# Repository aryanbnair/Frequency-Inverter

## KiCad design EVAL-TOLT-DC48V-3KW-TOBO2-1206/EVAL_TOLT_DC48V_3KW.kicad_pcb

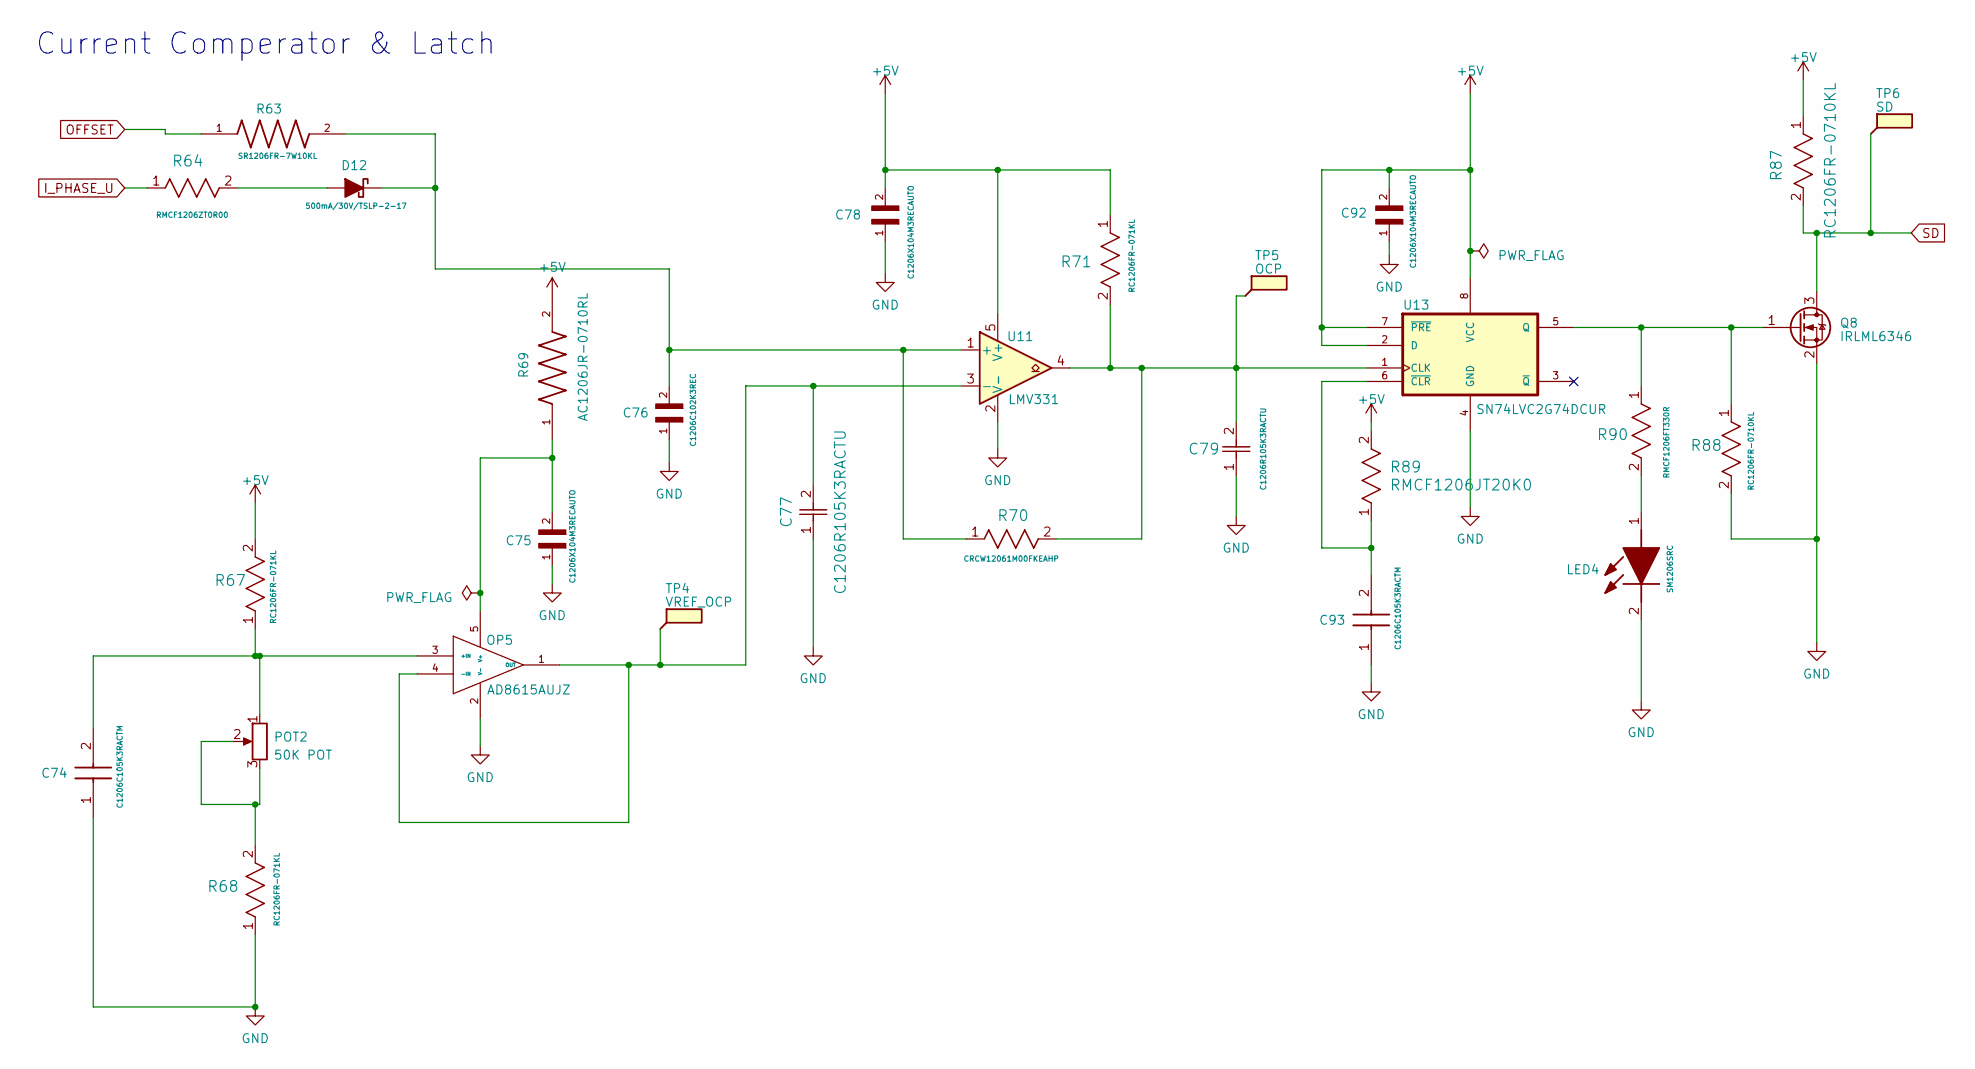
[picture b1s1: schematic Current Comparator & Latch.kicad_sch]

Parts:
C74, C93: C1206C105K3RACTM; C_1206_3216Metric; Mouser Part Number 80-C1206C105K3RACTM
C75, C78, C92: C1206X104M3RECAUTO; C_1206_3216Metric
C76: C1206C102K3REC; C_1206_3216Metric
C77, C79: C1206R105K3RACTU; C_1206_3216Metric
D12: 500mA/30V/TSLP-2-17; D_1206_3216Metric_Pad1.42x1.75mm_HandSolder
LED4: SM1206SRC; LED4; Mouser Part Number 749-SM1206SRC
OP5: AD8615AUJZ; AD8615; MPN AD8615AUJZ
POT2: 50K POT; POT2
Q8: IRLML6346; IRLML6346TRPBF
R63: SR1206FR-7W10KL; R_1206_3216Metric_Pad1.30x1.75mm_HandSolder
R64: RMCF1206ZT0R00; R_1206_3216Metric_Pad1.30x1.75mm_HandSolder
R67, R68, R71: RC1206FR-071KL; R_1206_3216Metric_Pad1.30x1.75mm_HandSolder
R69: AC1206JR-0710RL; R_1206_3216Metric_Pad1.30x1.75mm_HandSolder
R70: CRCW12061M00FKEAHP; R_1206_3216Metric_Pad1.30x1.75mm_HandSolder
R87, R88: RC1206FR-0710KL; R_1206_3216Metric_Pad1.30x1.75mm_HandSolder
R89: RMCF1206JT20K0; R_1206_3216Metric_Pad1.30x1.75mm_HandSolder
R90: RMCF1206FT330R; R_1206_3216Metric_Pad1.30x1.75mm_HandSolder
TP4: VREF_OCP; TestPoint_Bridge_Pitch2.54mm_Drill0.7mm
TP5: OCP; TestPoint_Bridge_Pitch2.54mm_Drill0.7mm
TP6: SD; TestPoint_Bridge_Pitch2.54mm_Drill0.7mm
U11: LMV331; LMV331M5
U13: SN74LVC2G74DCUR; SN74LVC2G74MDCUTEP

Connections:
+5V: C78.2, C92.2, R67.2, R69.2, R71.1, R87.1, R89.2, U11.5 (V+), U13.2 (D), U13.7 (~PRE), U13.8 (VCC); also elsewhere on the board
GND: C74.1, C75.1, C76.1, C77.1, C78.1, C79.1, C92.1, C93.1, LED4.2 (K), OP5.2 (V-), Q8.2 (S), R68.1, R88.2, U11.2 (V-), U13.4 (GND); also elsewhere on the board
I_PHASE_U: R64.1; also elsewhere on the board
unnamed: D12.2 (A), R64.2
unnamed: C76.2, D12.1 (K), R63.2, R70.1, U11.1 (+)
unnamed: LED4.1 (A), R90.2
unnamed: C74.2, OP5.3 (+IN), POT2.1, R67.1
unnamed: C77.2, OP5.1 (OUT), OP5.4 (-IN), TP4.1, U11.3 (-)
unnamed: C75.2, OP5.5 (V+), R69.1
unnamed: POT2.2, POT2.3, R68.2
unnamed: Q8.1 (G), R88.1, R90.1, U13.5 (Q)
unnamed: C79.2, R70.2, R71.2, TP5.1, U11.4, U13.1 (CLK)
unnamed: C93.2, R89.1, U13.6 (~CLR)
OFFSET: R63.1; also elsewhere on the board
SD: Q8.3 (D), R87.2, TP6.1; also elsewhere on the board

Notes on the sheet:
Current Comperator & Latch

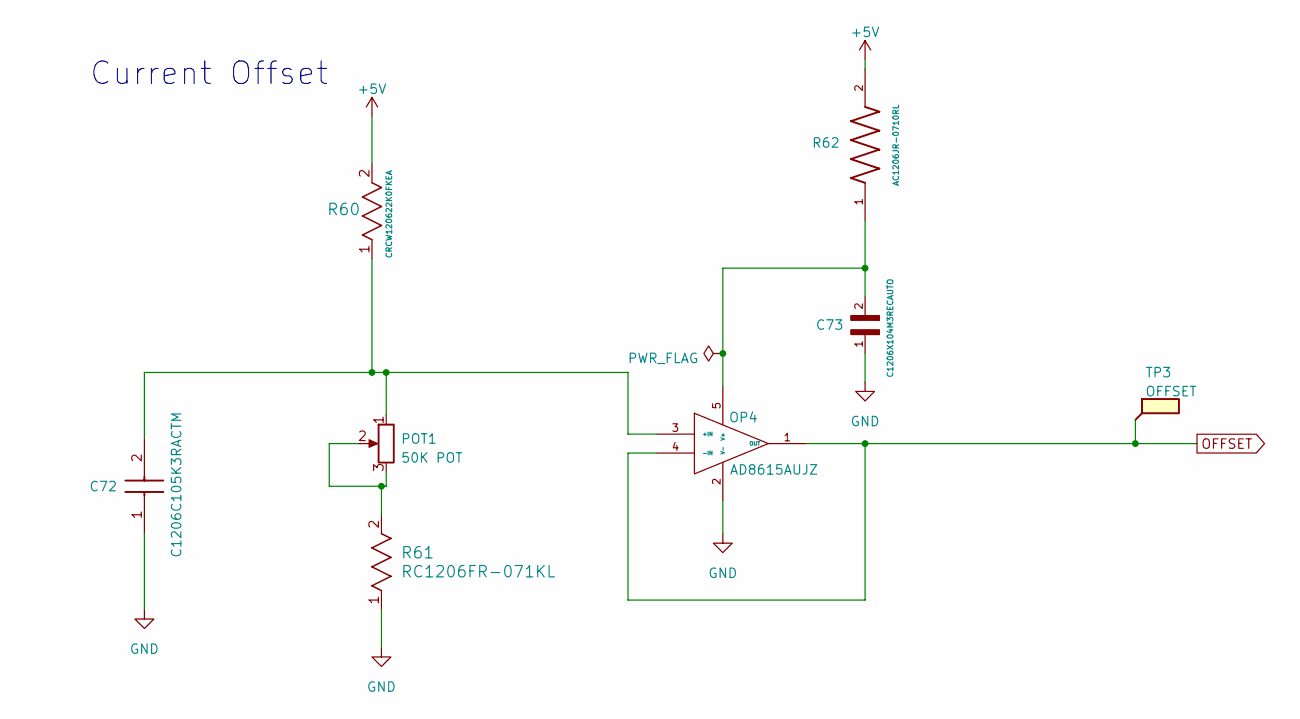
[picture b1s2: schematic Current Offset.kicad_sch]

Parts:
C72: C1206C105K3RACTM; C_1206_3216Metric; Mouser Part Number 80-C1206C105K3RACTM
C73: C1206X104M3RECAUTO; C_1206_3216Metric
OP4: AD8615AUJZ; AD8615; MPN AD8615AUJZ
POT1: 50K POT; POT2
R60: CRCW120622K0FKEA; R_1206_3216Metric_Pad1.30x1.75mm_HandSolder
R61: RC1206FR-071KL; R_1206_3216Metric_Pad1.30x1.75mm_HandSolder
R62: AC1206JR-0710RL; R_1206_3216Metric_Pad1.30x1.75mm_HandSolder
TP3: OFFSET; TestPoint_Bridge_Pitch2.54mm_Drill0.7mm

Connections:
+5V: R60.2, R62.2; also elsewhere on the board
GND: C72.1, C73.1, OP4.2 (V-), R61.1; also elsewhere on the board
unnamed: C72.2, OP4.3 (+IN), POT1.1, R60.1
unnamed: C73.2, OP4.5 (V+), R62.1
unnamed: POT1.2, POT1.3, R61.2
OFFSET: OP4.1 (OUT), OP4.4 (-IN), TP3.1; also elsewhere on the board

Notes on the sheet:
Current Offset

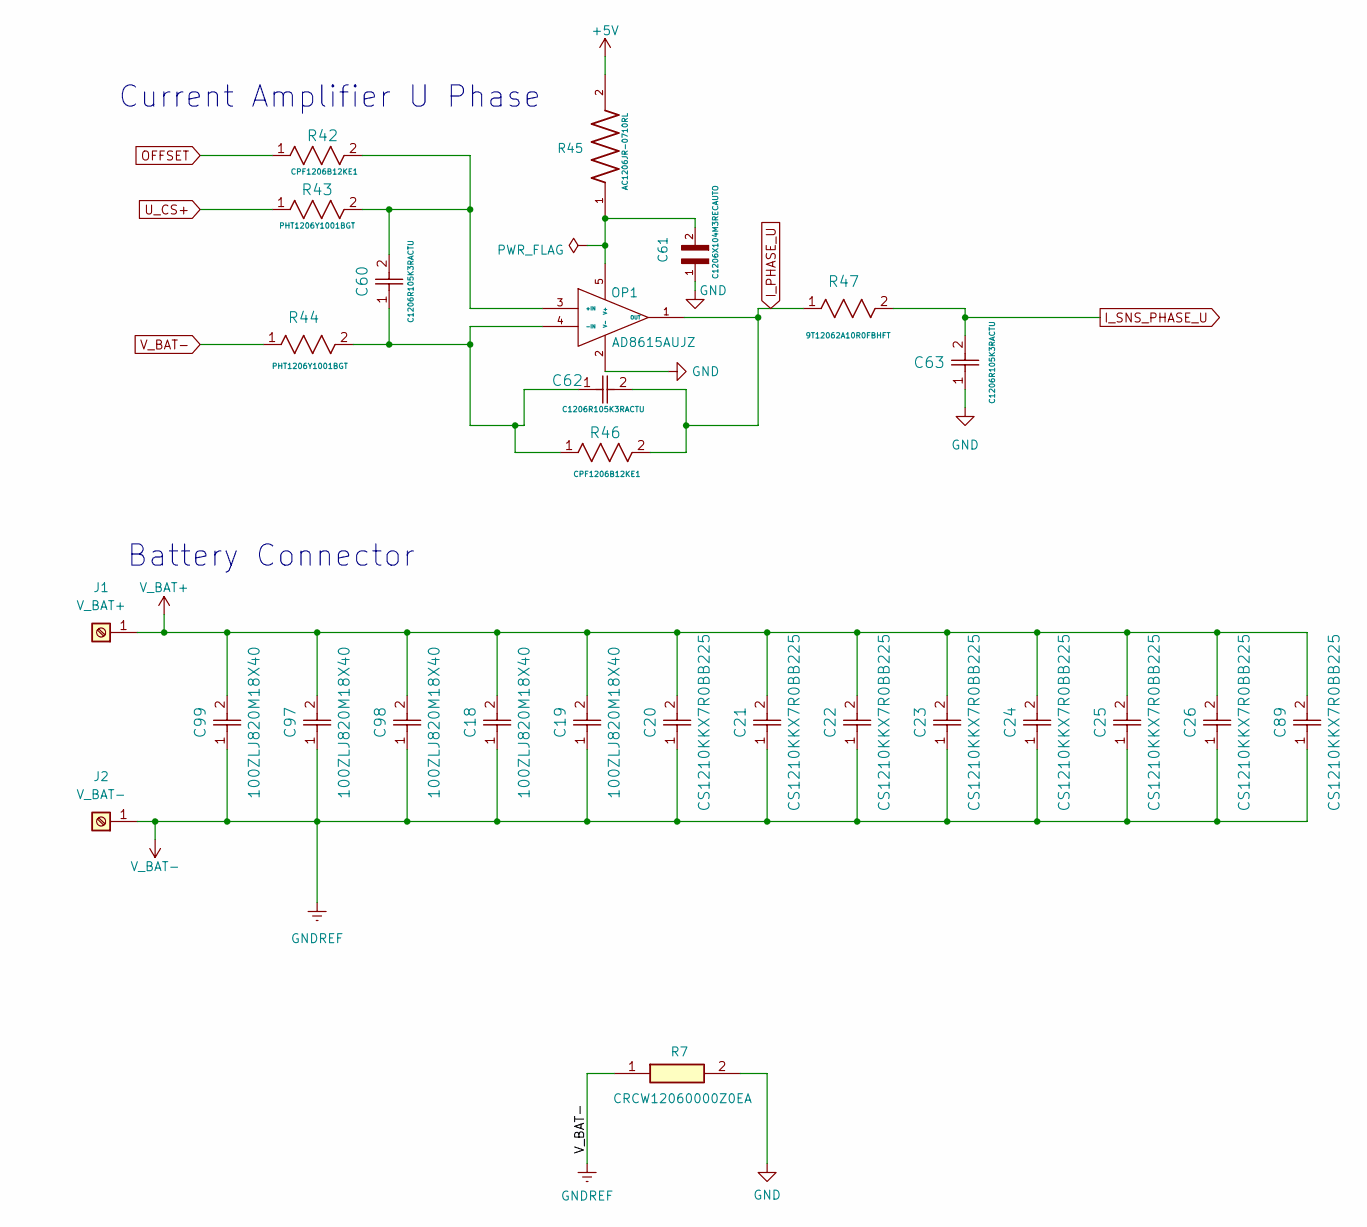
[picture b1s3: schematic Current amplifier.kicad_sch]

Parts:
C18, C19, C97, C98, C99: 100ZLJ820M18X40; C18
C20, C21, C22, C23, C24, C25, C26, C89: CS1210KKX7R0BB225; C_1206_3216Metric
C60, C62, C63: C1206R105K3RACTU; C_1206_3216Metric
C61: C1206X104M3RECAUTO; C_1206_3216Metric
J1: V_BAT+; J1
J2: V_BAT-; J1
OP1: AD8615AUJZ; AD8615; MPN AD8615AUJZ
R7: CRCW12060000Z0EA; R_1206_3216Metric_Pad1.30x1.75mm_HandSolder
R42, R46: CPF1206B12KE1; R_1206_3216Metric_Pad1.30x1.75mm_HandSolder
R43, R44: PHT1206Y1001BGT; R_1206_3216Metric_Pad1.30x1.75mm_HandSolder
R45: AC1206JR-0710RL; R_1206_3216Metric_Pad1.30x1.75mm_HandSolder
R47: 9T12062A10R0FBHFT; R_1206_3216Metric_Pad1.30x1.75mm_HandSolder

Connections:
+5V: R45.2; also elsewhere on the board
GND: C61.1, C63.1, OP1.2 (V-), R7.2; also elsewhere on the board
I_PHASE_U: C62.2, OP1.1 (OUT), R46.2, R47.1; also elsewhere on the board
I_SNS_PHASE_U: C63.2, R47.2; also elsewhere on the board
unnamed: C60.2, OP1.3 (+IN), R42.2, R43.2
unnamed: C60.1, C62.1, OP1.4 (-IN), R44.2, R46.1
unnamed: C61.2, OP1.5 (V+), R45.1
OFFSET: R42.1; also elsewhere on the board
U_CS+: R43.1; also elsewhere on the board
V_BAT+: C18.2, C19.2, C20.2, C21.2, C22.2, C23.2, C24.2, C25.2, C26.2, C89.2, C97.2, C98.2, C99.2, J1.1; also elsewhere on the board
V_BAT-: C18.1, C19.1, C20.1, C21.1, C22.1, C23.1, C24.1, C25.1, C26.1, C89.1, C97.1, C98.1, C99.1, J2.1, R7.1, R44.1; also elsewhere on the board

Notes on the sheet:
Battery Connector
Current Amplifier U Phase

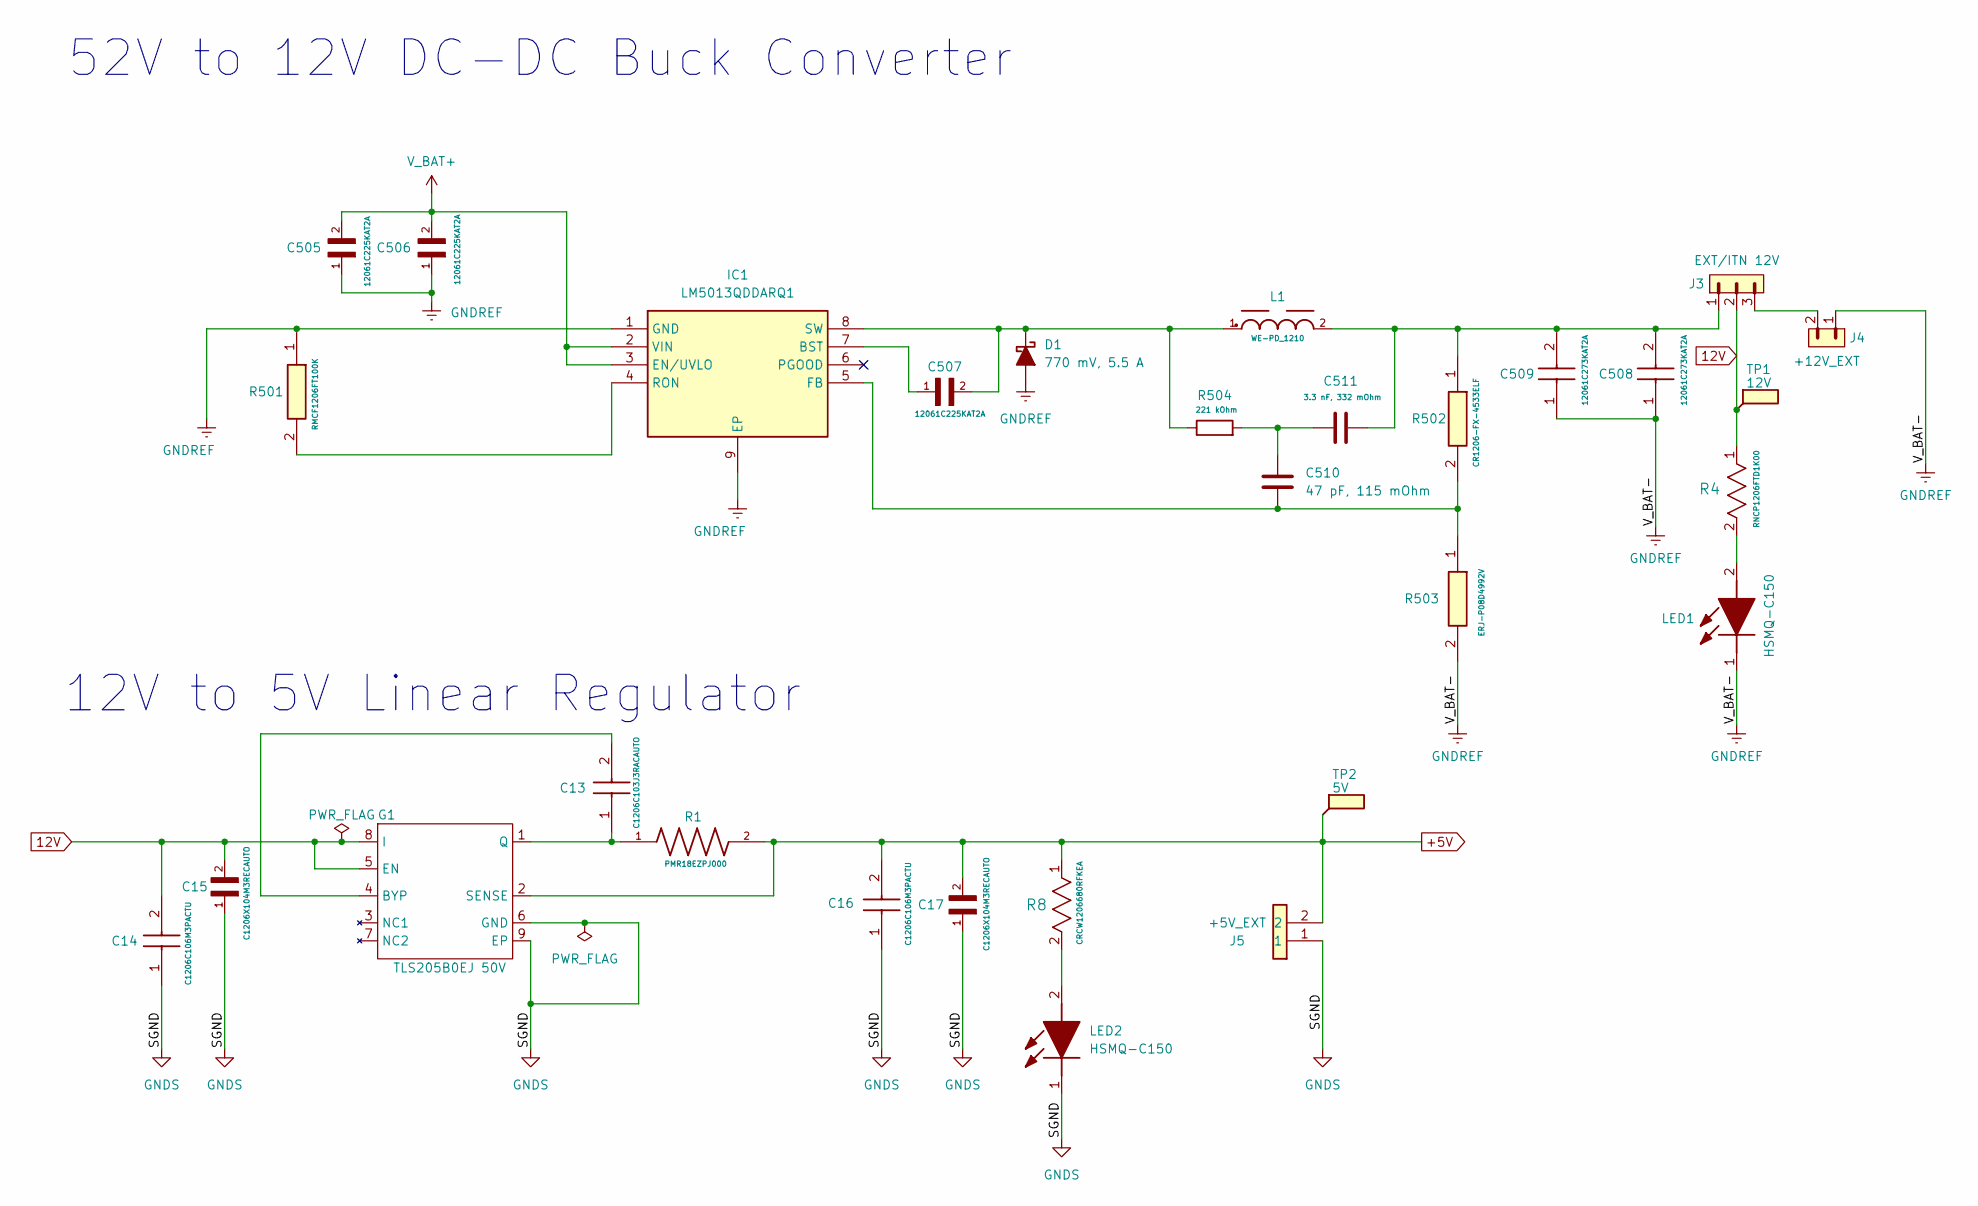
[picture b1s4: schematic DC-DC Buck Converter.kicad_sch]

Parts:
C13: C1206C103J3RACAUTO; C_1206_3216Metric
C14, C16: C1206C106M3PACTU; C_1206_3216Metric
C15, C17: C1206X104M3RECAUTO; C_1206_3216Metric
C505, C506: 12061C225KAT2A; C_1206_3216Metric
C507: 12061C225KAT2A; C_1206_3216Metric; Manufacturer_Part_Number 12061C273KAT2A
C508, C509: 12061C273KAT2A; C_1206_3216Metric; Manufacturer_Part_Number 12061C273KAT2A
C510: 47 pF, 115 mOhm; C_1206_3216Metric
C511: 3.3 nF, 332 mOhm; C_1206_3216Metric
D1: 770 mV, 5.5 A; D_1206_3216Metric
G1: TLS205B0EJ 50V; G1
IC1: LM5013QDDARQ1; DC; Mouser Part Number 595-LM5013QDDARQ1
J3: EXT/ITN 12V; PinHeader_1x03_P2.54mm_Vertical; PARTREV R
J4: +12V_EXT; PinHeader_1x02_P2.54mm_Vertical; Manufacturer_Part_Number 1725656; Mouser Part Number 651-1725656
J5: +5V_EXT; J4; Manufacturer_Part_Number 1725656; Mouser Part Number 651-1725656
L1: WE-PD_1210; L_1206_3216Metric_Pad1.22x1.90mm_HandSolder
LED1, LED2: HSMQ-C150; LED1; Mouser Part Number 630-HSMQ-C150
R1: PMR18EZPJ000; R_1206_3216Metric_Pad1.30x1.75mm_HandSolder
R4: RNCP1206FTD1K00; R_1206_3216Metric_Pad1.30x1.75mm_HandSolder
R8: CRCW1206680RFKEA; R_1206_3216Metric_Pad1.30x1.75mm_HandSolder
R501: RMCF1206FT100K; R_1206_3216Metric_Pad1.30x1.75mm_HandSolder; Mouser Part Number 708-RMCF1206FT100K
R502: CR1206-FX-4533ELF; R_1206_3216Metric_Pad1.30x1.75mm_HandSolder; Mouser Part Number 652-CR1206FX-4533ELF
R503: ERJ-P08D4992V; R_1206_3216Metric_Pad1.30x1.75mm_HandSolder; Mouser Part Number 667-ERJ-P08D4992V
R504: 221 kOhm; R_1206_3216Metric_Pad1.30x1.75mm_HandSolder
TP1: 12V; TestPoint_Bridge_Pitch2.54mm_Drill0.7mm
TP2: 5V; TestPoint_Bridge_Pitch2.54mm_Drill0.7mm

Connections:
12V: C14.2, C15.2, G1.5 (EN), G1.8 (I), J3.2, R4.1, TP1.1
+5V: C16.2, C17.2, G1.2 (SENSE), J5.2, R1.2, R8.1, TP2.1; also elsewhere on the board
GNDS: C14.1, C15.1, C16.1, C17.1, G1.6 (GND), G1.9 (EP), J5.1, LED2.1 (K); also elsewhere on the board
unnamed: C508.2 (C2), C509.2 (C2), C511.2, J3.1, L1.2, R502.1
unnamed: C510.1, C511.1, R504.2
unnamed: C507.2, D1.1 (K), IC1.8 (SW), L1.1, R504.1
unnamed: C13.2, G1.4 (BYP)
unnamed: C13.1, G1.1 (Q), R1.1
unnamed: C507.1, IC1.7 (BST)
unnamed: C510.2, IC1.5 (FB), R502.2, R503.1
unnamed: IC1.4 (RON), R501.2
unnamed: J3.3, J4.2
unnamed: LED1.2 (A), R4.2
unnamed: LED2.2 (A), R8.2
V_BAT+: C505.2, C506.2, IC1.2 (VIN), IC1.3 (EN/UVLO); also elsewhere on the board
V_BAT-: C505.1, C506.1, C508.1 (C1), C509.1 (C1), D1.2 (A), IC1.1 (GND), IC1.9 (EP), J4.1, LED1.1 (K), R501.1, R503.2; also elsewhere on the board

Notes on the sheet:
52V to 12V DC-DC Buck Converter
12V to 5V Linear Regulator

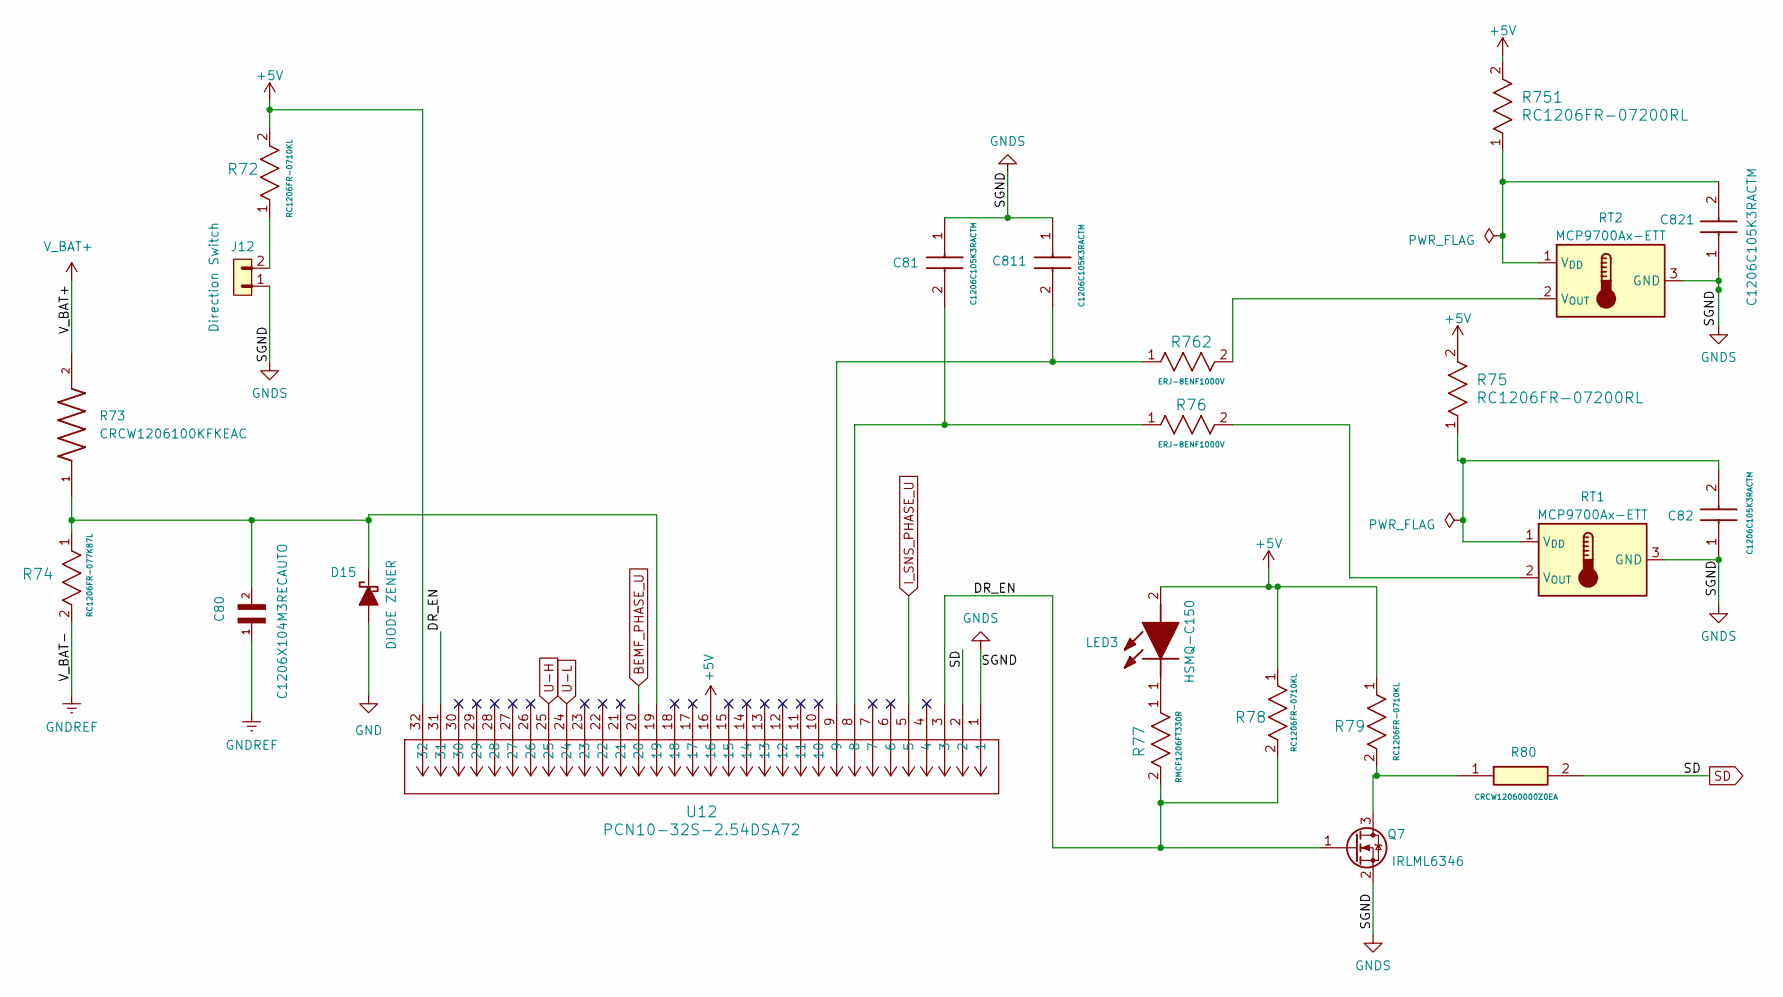
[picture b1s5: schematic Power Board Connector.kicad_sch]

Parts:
C80: C1206X104M3RECAUTO; C_1206_3216Metric
C81, C82, C811, C821: C1206C105K3RACTM; C_1206_3216Metric; Mouser Part Number 80-C1206C105K3RACTM
D15: DIODE ZENER; D_1206_3216Metric_Pad1.42x1.75mm_HandSolder
J12: Direction Switch; PinHeader_1x02_P2.54mm_Vertical; PARTREV R
LED3: HSMQ-C150; LED1; Mouser Part Number 630-HSMQ-C150
Q7: IRLML6346; IRLML6346TRPBF
R72, R78, R79: RC1206FR-0710KL; R_1206_3216Metric_Pad1.30x1.75mm_HandSolder
R73: CRCW1206100KFKEAC; R_1206_3216Metric_Pad1.30x1.75mm_HandSolder
R74: RC1206FR-077K87L; R_1206_3216Metric_Pad1.30x1.75mm_HandSolder
R75, R751: RC1206FR-07200RL; R_1206_3216Metric_Pad1.30x1.75mm_HandSolder
R76, R762: ERJ-8ENF1000V; R_1206_3216Metric_Pad1.30x1.75mm_HandSolder
R77: RMCF1206FT330R; R_1206_3216Metric_Pad1.30x1.75mm_HandSolder
R80: CRCW12060000Z0EA; R_1206_3216Metric_Pad1.30x1.75mm_HandSolder
RT1, RT2: MCP9700Ax-ETT; MCP9700AT_E_TT
U12: PCN10-32S-2.54DSA72; IDC-Header_2x17_P2.54mm_Vertical

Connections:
+5V: LED3.2 (A), R72.2, R75.2, R78.1, R79.1, R751.2, U12.16, U12.32; also elsewhere on the board
/Power Board Connector/DR_EN: Q7.1 (G), R77.2, R78.2, U12.3, U12.31
BEMF_PHASE_U: U12.20; also elsewhere on the board
GND: D15.2 (A); also elsewhere on the board
GNDS: C81.1, C82.1, C811.1, C821.1, J12.1, Q7.2 (S), RT1.3 (GND), RT2.3 (GND), U12.1; also elsewhere on the board
I_SNS_PHASE_U: U12.5; also elsewhere on the board
unnamed: C81.2, R76.1, U12.8
unnamed: C811.2, R762.1, U12.9
unnamed: C80.2, D15.1 (K), R73.1, R74.1, U12.19
unnamed: J12.2, R72.1
unnamed: LED3.1 (K), R77.1
unnamed: Q7.3 (D), R79.2, R80.1
unnamed: C82.2, R75.1, RT1.1 (V_{DD})
unnamed: R76.2, RT1.2 (V_{OUT})
unnamed: C821.2, R751.1, RT2.1 (V_{DD})
unnamed: R762.2, RT2.2 (V_{OUT})
SD: R80.2, U12.2; also elsewhere on the board
U-H: U12.25
U-L: U12.24; also elsewhere on the board
V_BAT+: R73.2; also elsewhere on the board
V_BAT-: C80.1, R74.2; also elsewhere on the board

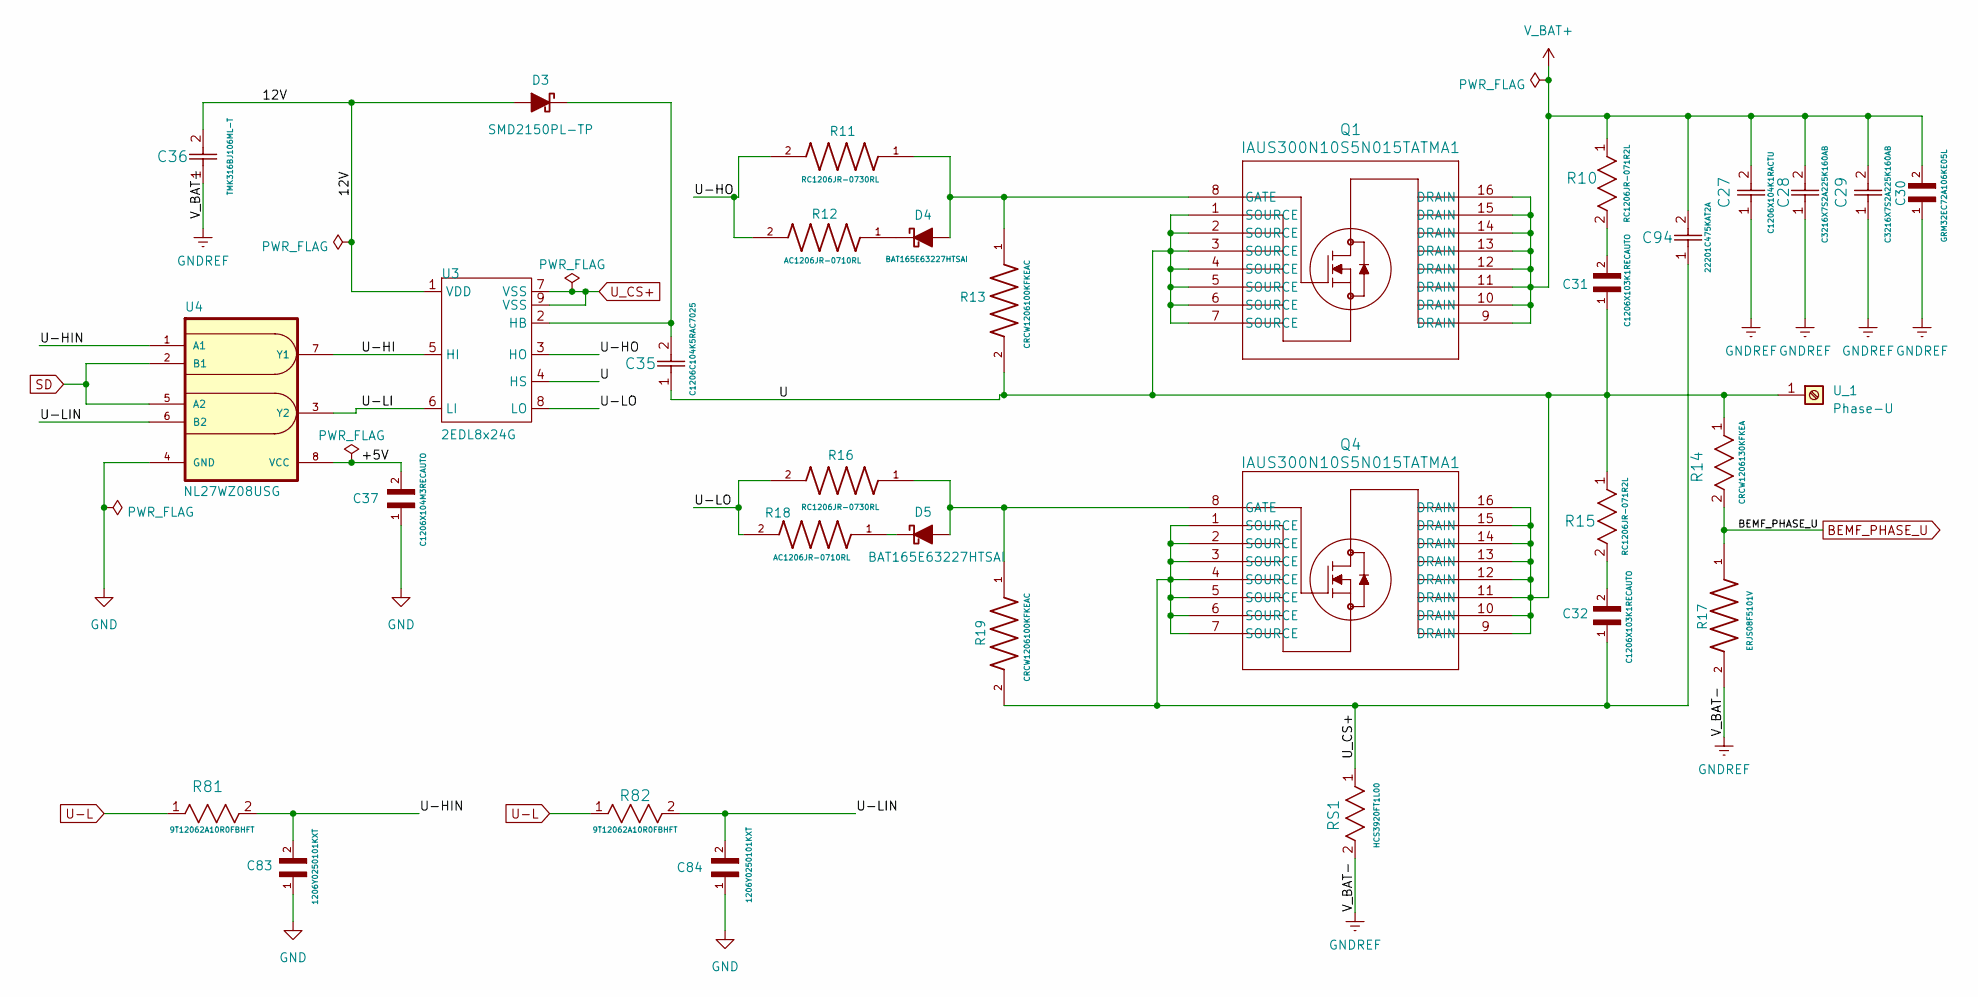
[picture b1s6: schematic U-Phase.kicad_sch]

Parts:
C27: C1206X104K1RACTU; C_1206_3216Metric
C28, C29: C3216X7S2A225K160AB; C_1206_3216Metric
C30: GRM32EC72A106KE05L; C_1206_3216Metric
C31, C32: C1206X103K1RECAUTO; C_1206_3216Metric
C35: C1206C104K5RAC7025; C_1206_3216Metric
C36: TMK316BJ106ML-T; C_1206_3216Metric
C37: C1206X104M3RECAUTO; C_1206_3216Metric
C83, C84: 1206Y0250101KXT; C_1206_3216Metric
C94: 22201C475KAT2A; C_1206_3216Metric
D3: SMD2150PL-TP; D_1206_3216Metric_Pad1.42x1.75mm_HandSolder
D4, D5: BAT165E63227HTSAI; D_1206_3216Metric_Pad1.42x1.75mm_HandSolder
Q1, Q4: IAUS300N10S5N015TATMA1; Q1
R10, R15: RC1206JR-071R2L; R_1206_3216Metric_Pad1.30x1.75mm_HandSolder
R11, R16: RC1206JR-0730RL; R_1206_3216Metric_Pad1.30x1.75mm_HandSolder
R12, R18: AC1206JR-0710RL; R_1206_3216Metric_Pad1.30x1.75mm_HandSolder
R13, R19: CRCW1206100KFKEAC; R_1206_3216Metric_Pad1.30x1.75mm_HandSolder
R14: CRCW1206130KFKEA; R_1206_3216Metric_Pad1.30x1.75mm_HandSolder
R17: ERJS08F5101V; R_1206_3216Metric_Pad1.30x1.75mm_HandSolder
R81, R82: 9T12062A10R0FBHFT; R_1206_3216Metric_Pad1.30x1.75mm_HandSolder
RS1: HCS3920FT1L00
U3: 2EDL8x24G; U3
U4: NL27WZ08USG; U4; MPN NL27WZ08USG
U_1: Phase-U; J1

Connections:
/U-Phase/12V: C36.2, D3.2 (A), U3.1 (VDD)
/U-Phase/+5V: C37.2, U4.8 (VCC)
/U-Phase/U: C31.1, C35.1, Q1.1 (SOURCE), Q1.2 (SOURCE), Q1.3 (SOURCE), Q1.4 (SOURCE), Q1.5 (SOURCE), Q1.6 (SOURCE), Q1.7 (SOURCE), Q4.9 (DRAIN), Q4.10 (DRAIN), Q4.11 (DRAIN), Q4.12 (DRAIN), Q4.13 (DRAIN), Q4.14 (DRAIN), Q4.15 (DRAIN), Q4.16 (DRAIN), R13.2, R14.1, R15.1, U3.4 (HS), U_1.1
/U-Phase/U-HI: U3.5 (HI), U4.7 (Y1)
/U-Phase/U-HIN: C83.2, R81.2, U4.1 (A1)
/U-Phase/U-HO: R11.2, R12.2, U3.3 (HO)
/U-Phase/U-LI: U3.6 (LI), U4.3 (Y2)
/U-Phase/U-LIN: C84.2, R82.2, U4.6 (B2)
/U-Phase/U-LO: R16.2, R18.2, U3.8 (LO)
BEMF_PHASE_U: R14.2, R17.1; also elsewhere on the board
GND: C37.1, C83.1, C84.1, U4.4 (GND); also elsewhere on the board
unnamed: C31.2, R10.2
unnamed: C32.2, R15.2
unnamed: C35.2, D3.1 (K), U3.2 (HB)
unnamed: D4.2 (A), Q1.8 (GATE), R11.1, R13.1
unnamed: D4.1 (K), R12.1
unnamed: D5.2 (A), Q4.8 (GATE), R16.1, R19.1
unnamed: D5.1 (K), R18.1
SD: U4.2 (B1), U4.5 (A2); also elsewhere on the board
U-L: R81.1, R82.1; also elsewhere on the board
U_CS+: C32.1, C94.1, Q4.1 (SOURCE), Q4.2 (SOURCE), Q4.3 (SOURCE), Q4.4 (SOURCE), Q4.5 (SOURCE), Q4.6 (SOURCE), Q4.7 (SOURCE), R19.2, RS1.1, U3.7 (VSS), U3.9 (VSS); also elsewhere on the board
V_BAT+: C27.2, C28.2, C29.2, C30.2, C94.2, Q1.9 (DRAIN), Q1.10 (DRAIN), Q1.11 (DRAIN), Q1.12 (DRAIN), Q1.13 (DRAIN), Q1.14 (DRAIN), Q1.15 (DRAIN), Q1.16 (DRAIN), R10.1; also elsewhere on the board
V_BAT-: C27.1, C28.1, C29.1, C30.1, C36.1, R17.2, RS1.2; also elsewhere on the board

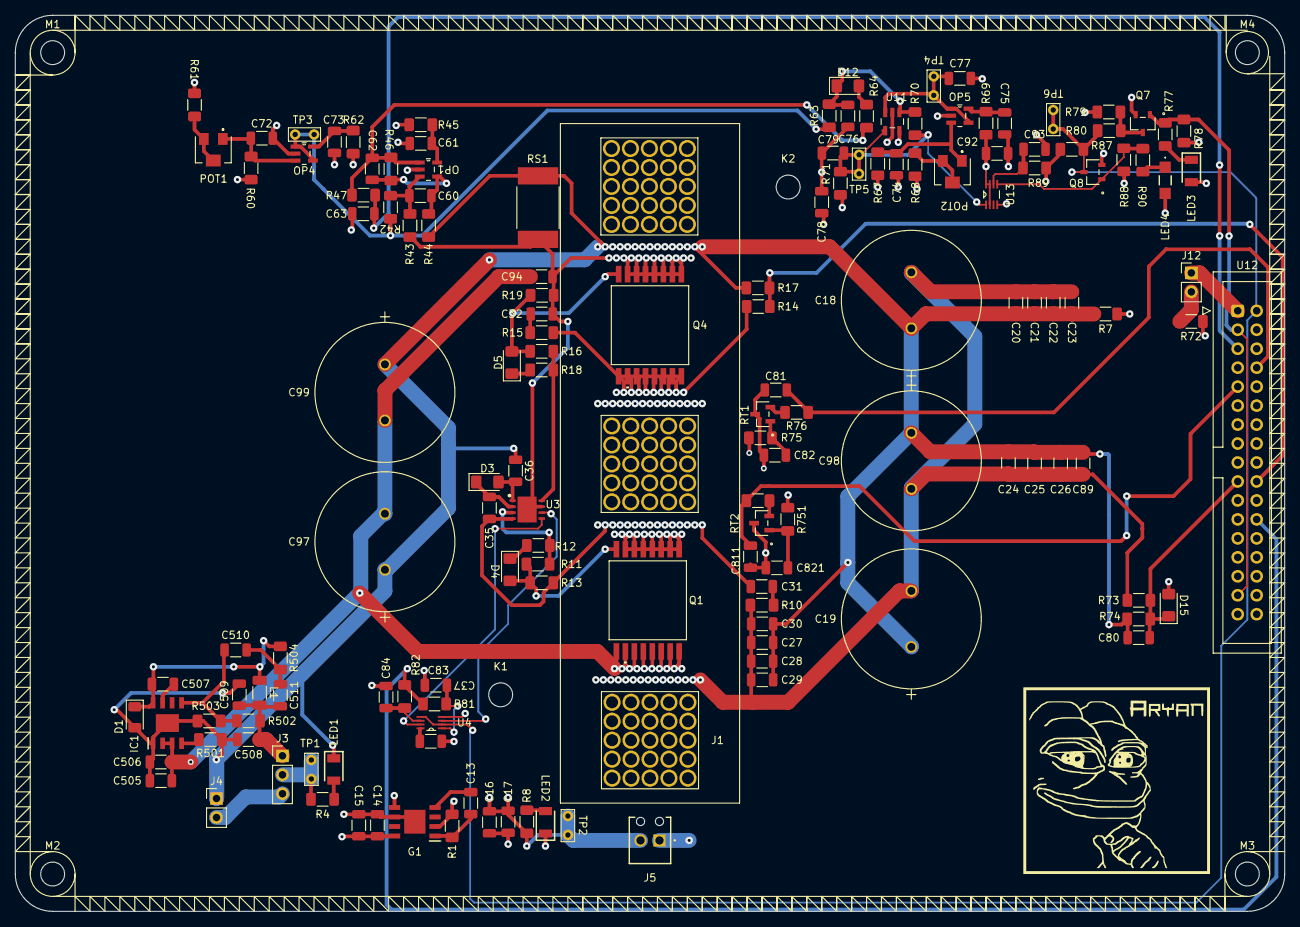
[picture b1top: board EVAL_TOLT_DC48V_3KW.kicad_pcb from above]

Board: 6 copper layers, 170.0 x 120.0 mm, 157 parts (0 on the bottom side), 67 nets.

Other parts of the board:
K1, K2: MountingHole_3.2mm_M3_DIN965
LOGO: LOGO; Aryan-Pepe-Logo
M1, M2, M3, M4: MountingHole_3.2mm_M3_DIN965

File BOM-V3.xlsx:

# | Reference | Component Number | Qty | Price
1 | C13 | C1206C103J3RACAUTO | 1 | 0.28
2 | C14,C16 | C1206C106M3PACTU | 2 | 0.25
3 | C15,C17,C37,C61,C73,C75,C78,C80,C92 | C1206X104M3RECAUTO | 9 | 0.09
4 | C18,C19,C97,C98,C99 | 100ZLJ820M18X40 | 5 | 3.96
5 | C20,C21,C22,C23,C24,C25,C26,C89 | CS1210KKX7R0BB225 | 8 | 0.63
6 | C27 | C1206X104K1RACTU | 1 | 0.39
7 | C28,C29 | C3216X7S2A225K160AB | 2 | 0.64
8 | C30 | GRM32EC72A106KE05L | 1 | 1.31
9 | C31,C32 | C1206X103K1RECAUTO | 2 | 0.08
10 | C33,C34 | opt/0603/25V | 2
11 | C35 | C1206C104K5RAC7025 | 1 | 0.12
12 | C36 | TMK316BJ106ML-T | 1 | 0.22
13 | C60,C62,C63,C77,C79 | C1206R105K3RACTU | 5 | 3.43
14 | C72,C74,C81,C82,C93 | C1206C105K3RACTM | 5 | 0.214
15 | C76 | C1206C102K3REC | 1 | 0.03
16 | C83,C84 | 1206Y0250101KXT | 2 | 0.2
17 | C94 | 22201C475KAT2A | 1 | 1.85
18 | C506 | 2.2 uF XXV 1206 | 1
19 | C507 | 2.2 nF XXV 1206 | 1
20 | C508 | 27 nF XXV 1206 | 1
21 | D3 | SMD2150PL-TP | 1 | 0.3
22 | D4,D5 | BAT165E63227HTSA1 | 2 | 0.4
23 | D12 | PMEG3005ELD,315 | 1 | 0.3
24 | D15 | BZX384-B5V1,115 | 1 | 0.12
25 | G1 | TLS205B0EJ 50V | 1 | 1.8
26 | IC1 | LM5013QDDARQ1 | 1 | 5.31
27 | J1 | V_BAT+ | 1
28 | J2 | V_BAT- | 1
29 | J5 | +5V_EXT | 1
30 | J12 | Direction Switch | 1
31 | L1 | WE-PD_1210 | 1 | 2.71
32 | LED1,LED2,LED3 | HSMQ-C150 | 3 | 1.25
33 | LED4 | SM1206SRC | 1 | 0.13
34 | OP1,OP4,OP5 | AD8615AUJZ | 3 | 5.06
35 | POT1,POT2 | SM42TW503 | 2 | 4.01
36 | Q1,Q4 | IAUS300N10S5N015TATMA1 | 2 | 5.42
37 | Q7,Q8 | IRLML6346 | 2 | 0.4
38 | R1 | PMR18EZPJ000 | 1 | 0.86
39 | R4 | RNCP1206FTD1K00 | 1 | 0.09
40 | R7,R80 | CRCW12060000Z0EA | 2 | 0.09
41 | R8 | CRCW1206680RFKEA | 1 | 0.09
42 | R10,R15 | RC1206JR-071R2L | 2 | 0.13
43 | R11,R16 | RC1206JR-0730RL | 2 | 0.09
44 | R12,R18,R45,R62,R69 | AC1206JR-0710RL | 5 | 0.11
45 | R13,R19,R73 | CRCW1206100KFKEAC | 3 | 0.09
46 | R14 | CRCW1206130KFKEA | 1 | 0.09
47 | R17 | ERJS08F5101V | 1 | ( Bulk )( 316 )
48 | R42,R46 | CPF1206B12KE1 | 2 | 0.14
49 | R43,R44 | PHT1206Y1001BGT | 2 | 12.01
50 | R47,R81,R82 | 9T12062A10R0FBHFT | 3 | 0.09
51 | R60 | CRCW120622K0FKEA | 1 | 0.09
52 | R61,R67,R68,R71 | RC1206FR-071KL | 4 | 0.09
53 | R63 | SR1206FR-7W10KL | 1 | 0.09
54 | R64 | RMCF1206ZT0R00 | 1 | 0.09
55 | R70 | CRCW12061M00FKEAHP | 1 | 0.21
56 | R72,R78,R79,R87,R88 | RC1206FR-0710KL | 5 | 0.09
57 | R74 | RC1206FR-077K87L | 1 | 0.09
58 | R75 | RC1206FR-07200RL | 1 | 0.09
59 | R76 | ERJ-8ENF1000V | 1 | 0.16
60 | R77,R90 | RMCF1206FT330R | 2 | 0.09
61 | R89 | RMCF1206JT20K0 | 1 | 0.09
62 | R501 | 100k 0603 | 1
63 | R502 | 453k 1206 | 1
64 | R503 | 49.9k 1206 | 1
65 | RS1 | HCS3920FT1L00 | 1 | 0.09
66 | RT1 | MCP9700Ax-ETT | 1 | 0.35
67 | TP1 | 12V | 1
68 | TP2 | 5V | 1
69 | TP3 | OFFSET | 1
70 | TP4 | VREF_OCP | 1
71 | TP5 | OCP | 1
72 | TP6 | SD | 1
73 | U3 | 2EDL8x24G | 1 | CANT FIND
74 | U4 | NL27WZ08USG | 1 | 0.63
75 | U11 | LMV331 | 1 | 0.9
76 | U12 | PCN10C-32S-2.54DS(72) | 1 | 3.86
77 | U13 | SN74LVC2G74DCUR | 1 | 0.38
78 | U_1 | Phase-U | 1
